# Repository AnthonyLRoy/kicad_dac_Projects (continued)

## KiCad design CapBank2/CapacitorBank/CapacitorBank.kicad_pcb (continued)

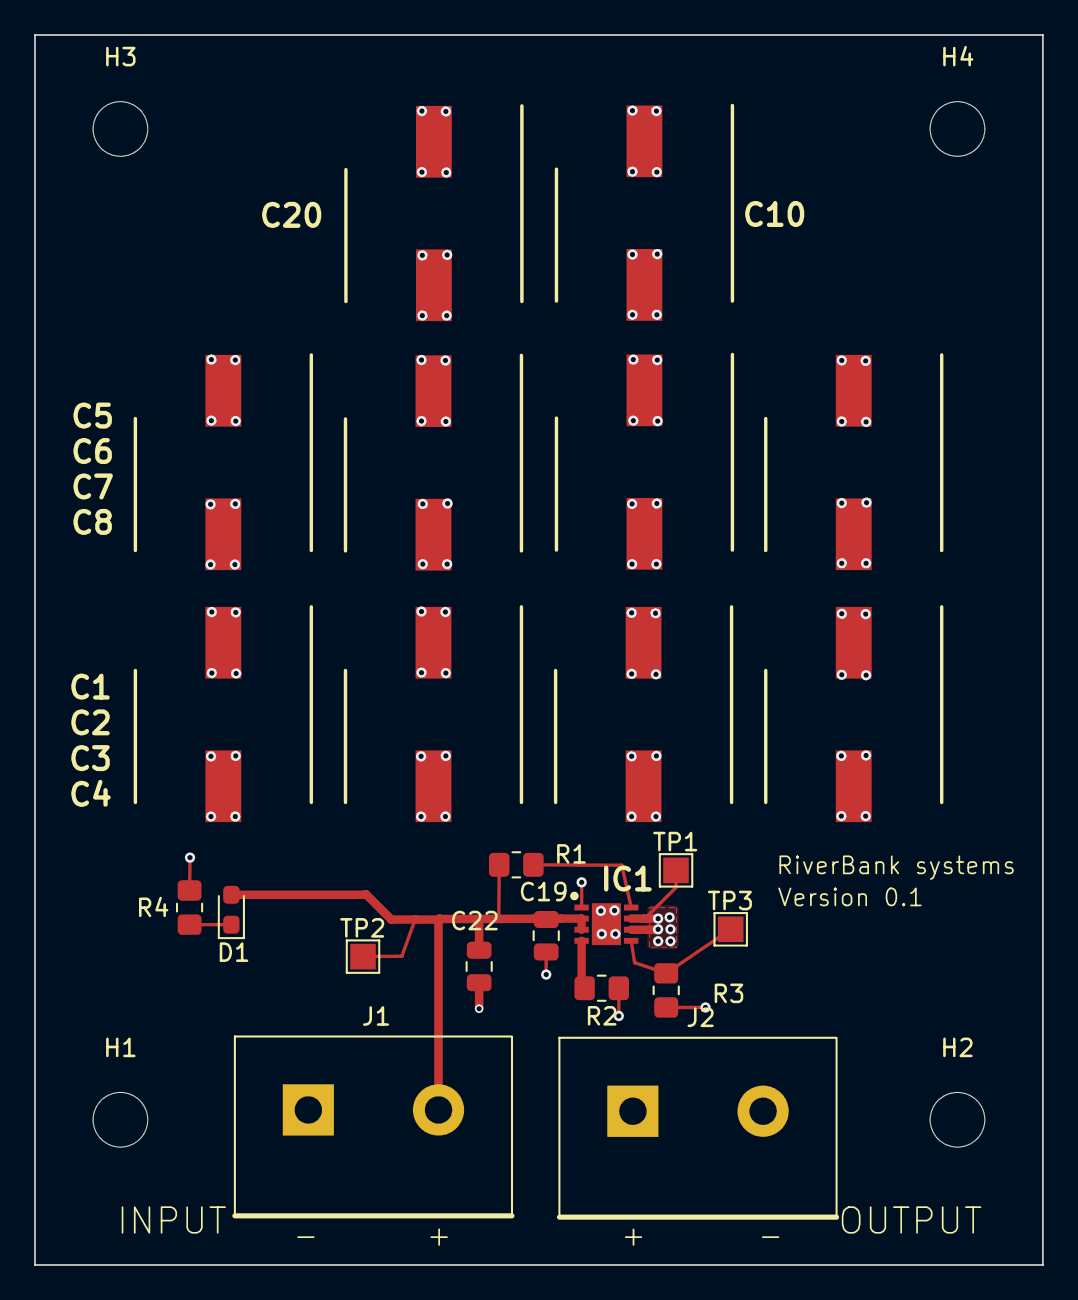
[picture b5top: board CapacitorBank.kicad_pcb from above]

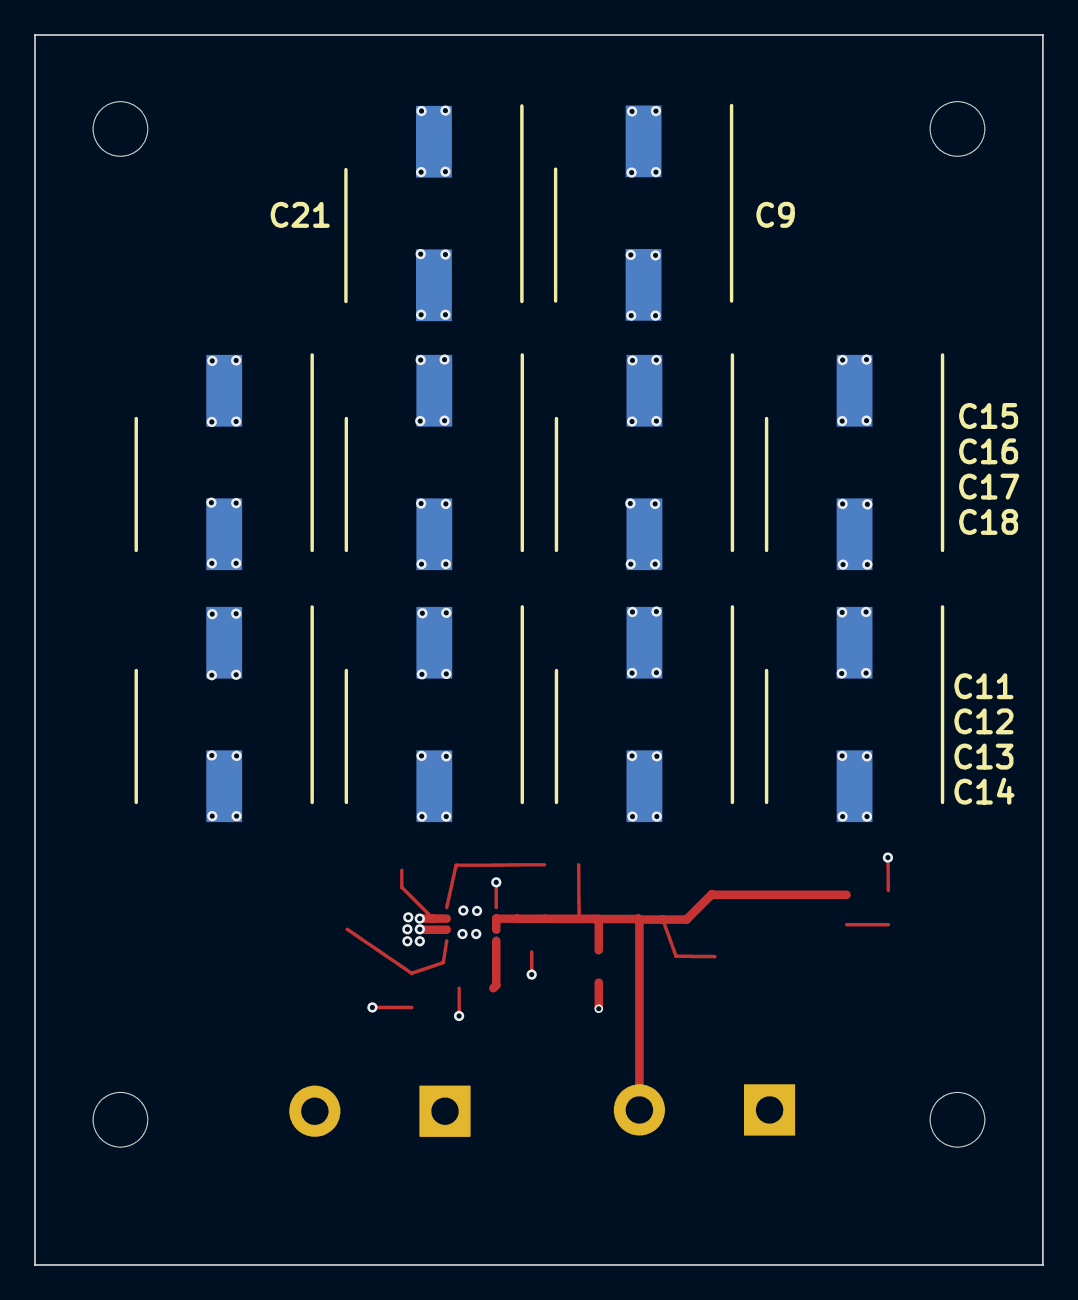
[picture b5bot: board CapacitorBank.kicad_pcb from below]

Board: 4 copper layers, 59.0 x 72.0 mm, 37 parts (10 on the bottom side), 7 nets.

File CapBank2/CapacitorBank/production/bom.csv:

Designator,Footprint,Quantity,Value,LCSC Part #
"C1, C10, C11, C12, C13, C14, C15, C16, C17, C18, C2, C20, C21, C3, C4, C5, C6, C7, C8, C9",CAPAE1030X1270N,20,875075361005,
C19,0805,1,0.1uf,
C22,0805,1,47u,
D1,0603,1,LED,
"H1, H2, H3, H4",MountingHole_3.2mm_M3,4,MountingHole,
IC1,SON65P300X300X100-9N-D,1,TPS2556QDRBTQ1,
"J1, J2",TerminalBlock_483132_2P_P7.62mm,2,Screw_Terminal_01x02,
R1,0805,1,100k,
R2,0805,1,10k,
R3,0805,1,160k,
R4,0805,1,1k,
"TP1, TP2, TP3",TestPoint_Pad_1.5x1.5mm,3,TestPoint,

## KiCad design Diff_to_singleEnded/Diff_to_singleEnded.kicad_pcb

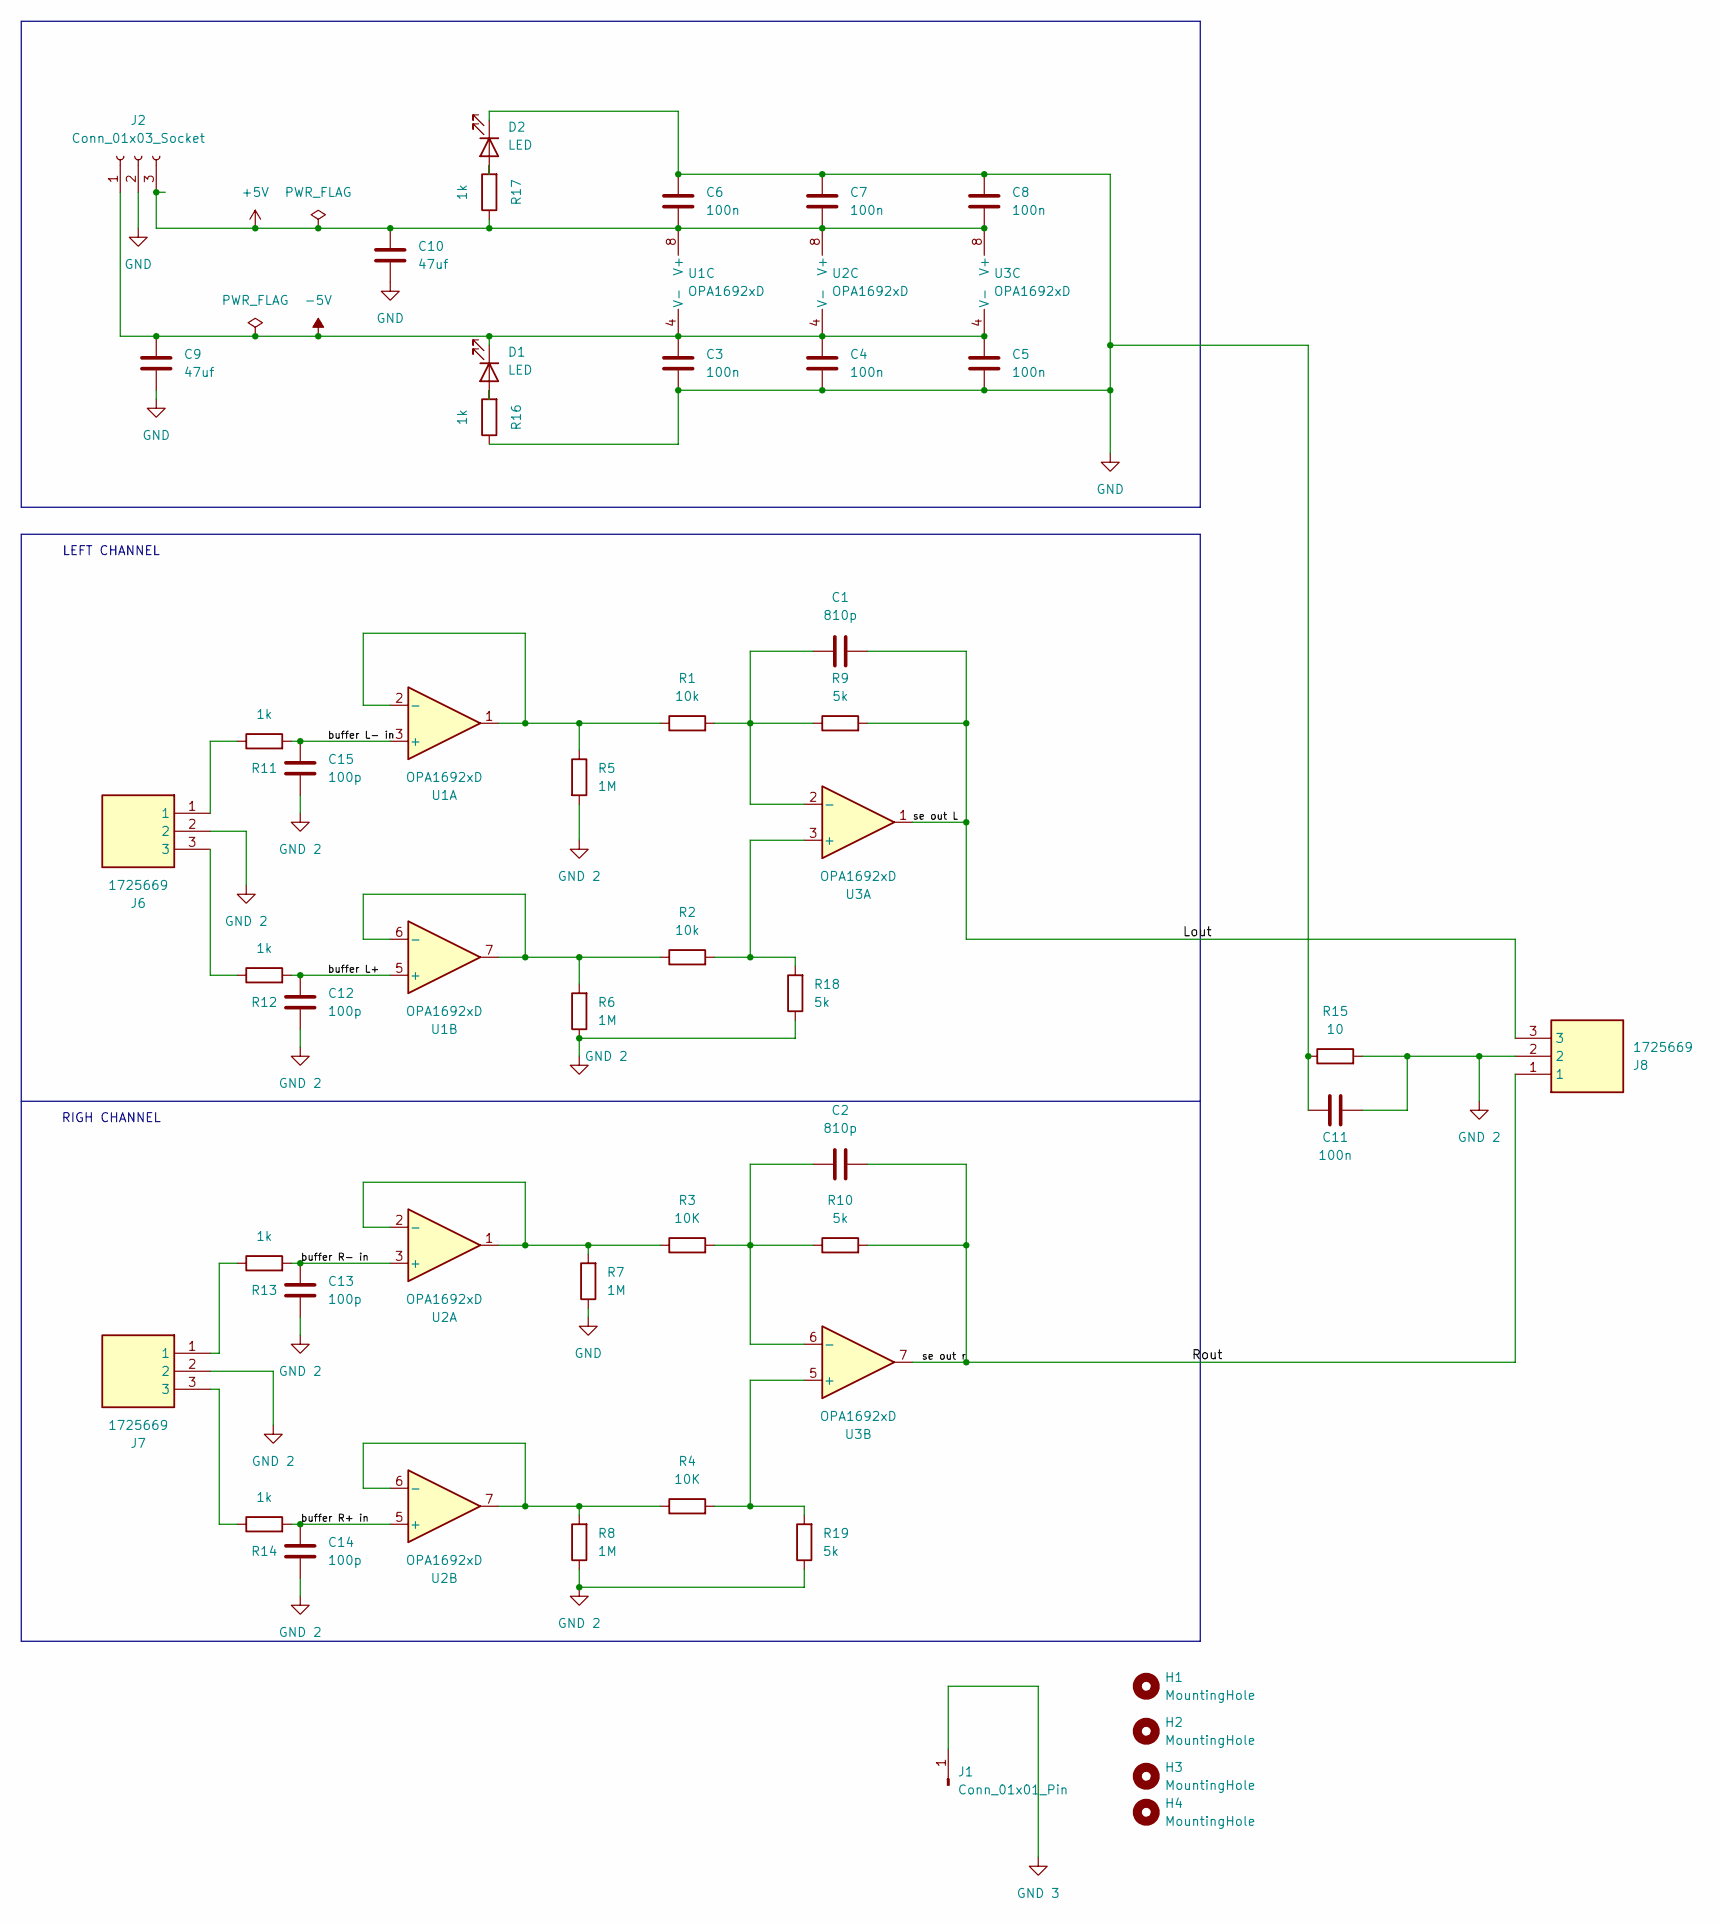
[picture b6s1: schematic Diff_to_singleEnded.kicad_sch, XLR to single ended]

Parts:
C1, C2: 810p; C_1206_3216Metric
C3, C4, C5, C6, C7, C8, C11: 100n; C_0805_2012Metric_Pad1.18x1.45mm_HandSolder
C9, C10: 47uf; CAPC3225X280N
C12, C13, C14, C15: 100p; C_0805_2012Metric
D1, D2: LED; LEDC2012X40N
H1, H2, H3, H4: MountingHole; MountingHole_2.7mm_M2.5
J1: Conn_01x01_Pin; PinHeader_1x01_P1.00mm_Vertical
J2: Conn_01x03_Socket; PhoenixContact_MCV_1,5_3-G-3.81_1x03_P3.81mm_Vertical
J6, J7, J8: 1725669; Mouser Part Number 651-1725669
R1, R2: 10k; R_Axial_DIN0309_L9.0mm_D3.2mm_P12.70mm_Horizontal
R3, R4: 10K; R_Axial_DIN0309_L9.0mm_D3.2mm_P12.70mm_Horizontal
R5, R6, R7, R8: 1M; R_Axial_DIN0309_L9.0mm_D3.2mm_P12.70mm_Horizontal
R9, R10, R18, R19: 5k; R_Axial_DIN0309_L9.0mm_D3.2mm_P12.70mm_Horizontal
R11, R12, R13, R14, R16, R17: 1k; R_0805_2012Metric
R15: 10; R_0603_1608Metric
U1, U2, U3: OPA1692xD; SOIC-8_3.9x4.9mm_P1.27mm

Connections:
+5V: C6.2, C7.2, C8.2, C10.1, J2.3, R17.1, U1.8 (V+), U2.8 (V+), U3.8 (V+)
-5V: C3.1, C4.1, C5.1, C9.1, D1.1 (K), J2.1, U1.4 (V-), U2.4 (V-), U3.4 (V-)
/Lout: C1.2, J8.3, R9.2, U3.1
/Rout: C2.2, J8.1, R10.2, U3.7
/buffer L+: C12.2, R12.2, U1.5 (+)
/buffer L- in: C15.2, R11.2, U1.3 (+)
/buffer R+ in: C14.2, R14.2, U2.5 (+)
/buffer R- in: C13.2, R13.2, U2.3 (+)
GND: C3.2, C4.2, C5.2, C6.1, C7.1, C8.1, C9.2, C10.2, C11.1, D2.1 (K), J2.2, R7.1, R15.1, R16.1
GND 2: C11.2, C12.1, C13.1, C14.1, C15.1, J6.2, J7.2, J8.2, R5.2, R6.1, R8.1, R15.2, R18.1, R19.1
GND 3: J1.1 (Pin_1_1)
unnamed: D1.2 (A), R16.2
unnamed: D2.2 (A), R17.2
unnamed: J6.1, R11.1
unnamed: J6.3, R12.1
unnamed: J7.1, R13.1
unnamed: J7.3, R14.1
unnamed: R1.1, R5.1, U1.1, U1.2 (-)
unnamed: R2.1, R6.2, U1.6 (-), U1.7
unnamed: R3.1, R7.2, U2.1, U2.2 (-)
unnamed: R4.1, R8.2, U2.6 (-), U2.7
unnamed: R2.2, R18.2, U3.3 (+)
unnamed: C1.1, R1.2, R9.1, U3.2 (-)
unnamed: R4.2, R19.2, U3.5 (+)
unnamed: C2.1, R3.2, R10.1, U3.6 (-)

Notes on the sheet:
LEFT CHANNEL
RIGH CHANNEL

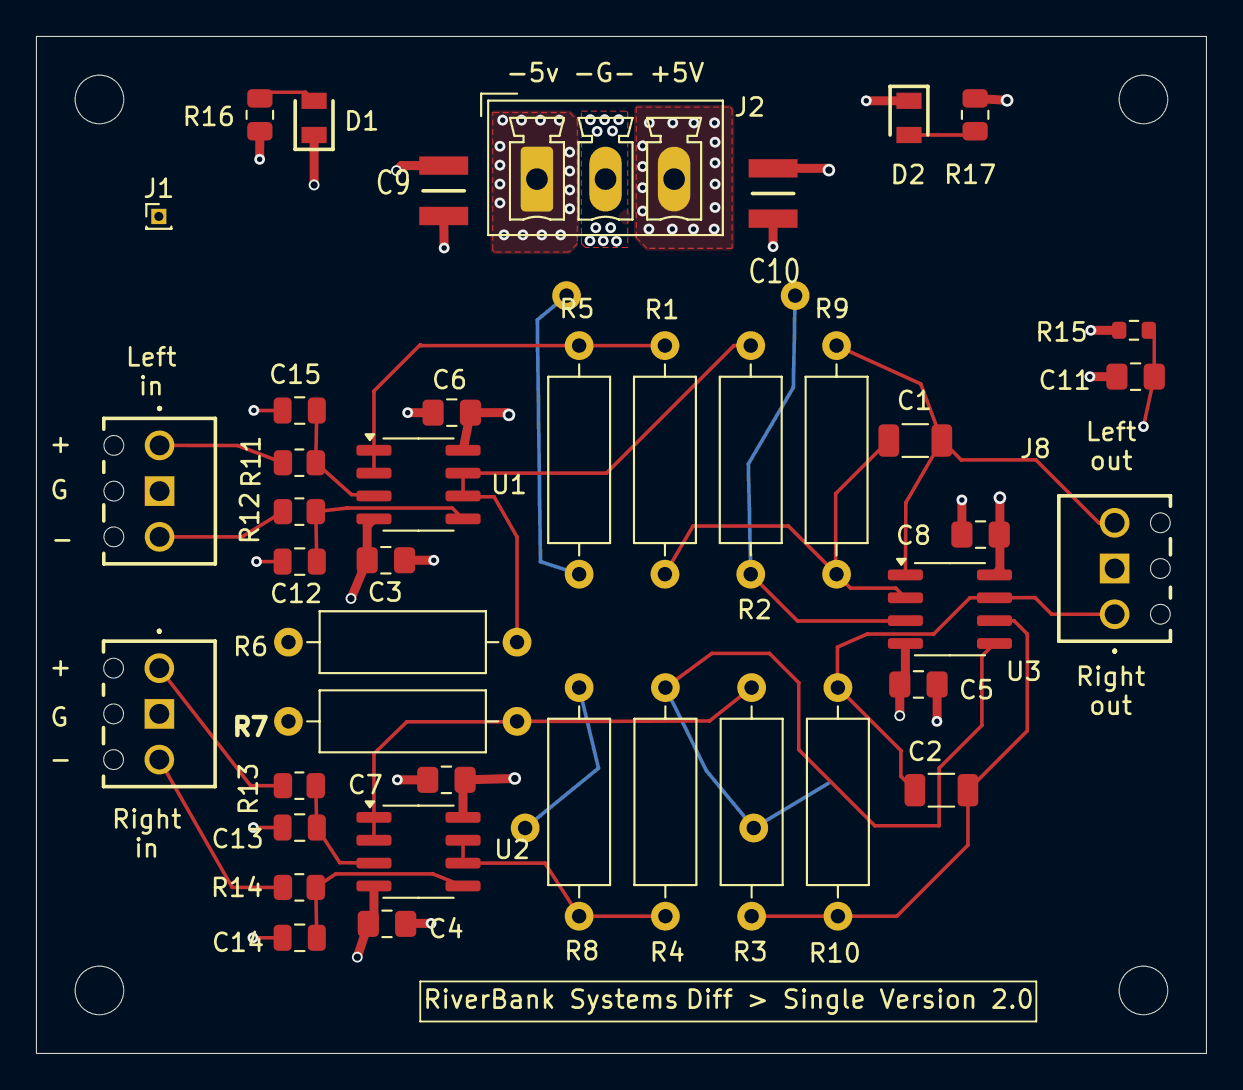
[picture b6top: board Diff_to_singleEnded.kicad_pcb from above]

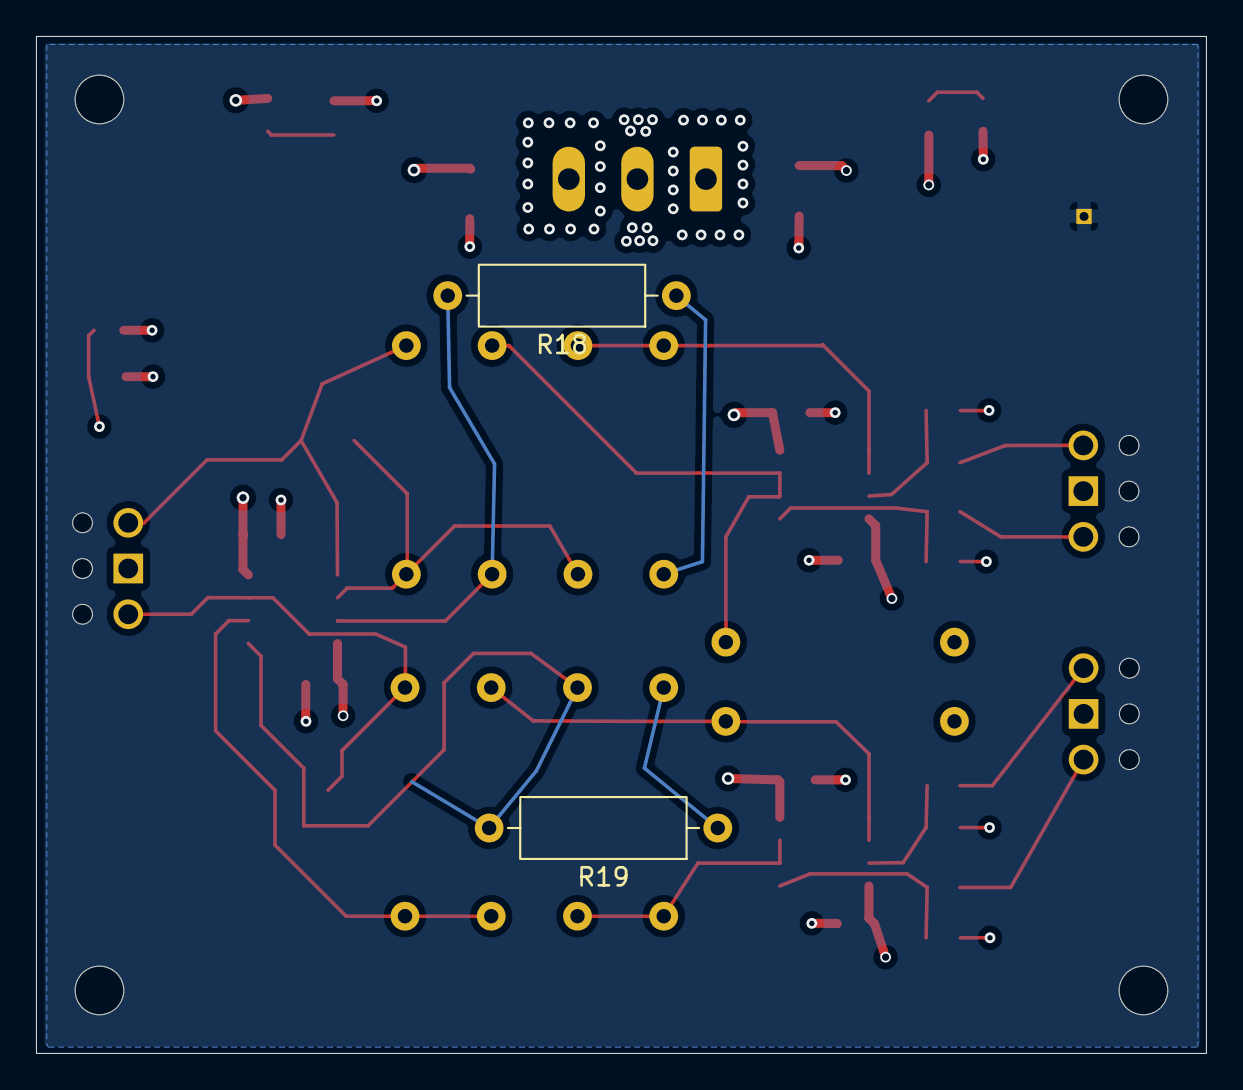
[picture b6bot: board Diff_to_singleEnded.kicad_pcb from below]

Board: 6 copper layers, 65.0 x 56.5 mm, 48 parts (2 on the bottom side), 24 nets.

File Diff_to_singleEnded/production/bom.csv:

Designator,Footprint,Quantity,Value,LCSC Part #
"C1, C2",1206,2,810p,
"C10, C9",CAPC3225X280N,2,47uf,
"C11, C3, C4, C5, C6, C7, C8",0805,7,100n,
"C12, C13, C14, C15",0805,4,100p,
"D1, D2",LEDC2012X40N,2,LED,
"H1, H2, H3, H4",MountingHole_2.7mm_M2.5,4,MountingHole,
J1,PinHeader_1x01_P1.00mm_Vertical,1,Conn_01x01_Pin,
J2,"PhoenixContact_MCV_1,5_3-G-3.81_1x03_P3.81mm_Vertical",1,Conn_01x03_Socket,
"J6, J7, J8",1725669,3,1725669,
"R1, R2, R3, R4",R_Axial_DIN0309_L9.0mm_D3.2mm_P12.70mm_Horizontal,4,10k,
"R10, R9",R_Axial_DIN0309_L9.0mm_D3.2mm_P12.70mm_Horizontal,2,5k,
"R11, R12, R13, R14, R16, R17",0805,6,1k,
R15,0603,1,10,
"R5, R6, R7, R8",R_Axial_DIN0309_L9.0mm_D3.2mm_P12.70mm_Horizontal,4,1M,
"U1, U2, U3",SOIC-8_3.9x4.9mm_P1.27mm,3,OPA1692xD,

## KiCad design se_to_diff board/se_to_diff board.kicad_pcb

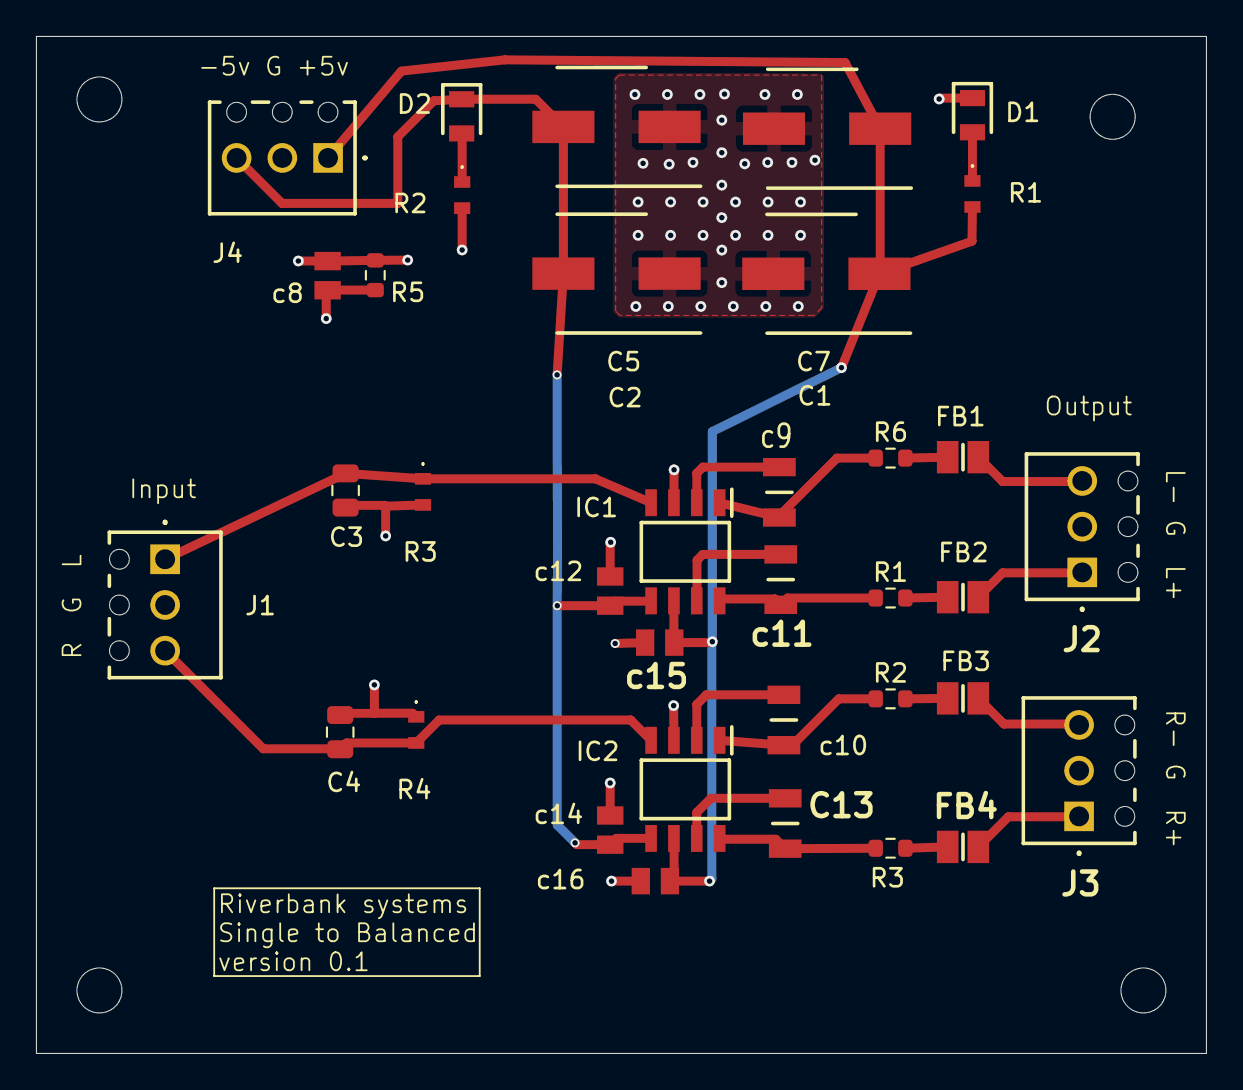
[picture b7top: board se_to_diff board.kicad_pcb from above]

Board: 4 copper layers, 65.0 x 56.5 mm, 40 parts (0 on the bottom side), 24 nets.

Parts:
C1, C2, C5, C7: 47u; CAPAE660X800N
C3, C4: 220p; C_0805_2012Metric
C13: 10u; CAPC3216X229N
D1, D2: LS_R976; LEDC2012X40N
FB1, FB2, FB3, FB4: NFZ2MSD101SZ10L; BEADC2016X120N
H1, H2, H3, H4: MountingHole; MountingHole_2.5mm
IC1, IC2: 1646S08-U; SOIC127P602X173-8N
J1, J2, J3, J4: 1725669
R1, R2#2, R3: 22; R_0603_1608Metric
R1#2, R2: 3k; ERJH3
R3#2, R4: 47k; ERJH3
R5: 10R; R_0603_1608Metric
R6: 22R; R_0603_1608Metric
c8, c12, c14, c15, c16: 100n; CAPC2012X94N
c9, c10, c11: 10u; CAPC3216X229N

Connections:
/Sout L +: FB2.1, R1.2
/Sout L -: FB1.1, R6.2
/Sout R +: FB4.1, R3.2
/Sout R -: FB3.1, R2#2.2
/in L: C3.2, IC1.4 (IN), J1.1, R3#2.1
/in R: C4.1, IC2.4 (IN), J1.3, R4.2
/out L +: IC1.8 (OUT+), R1.1, c11.2
/out L -: IC1.1 (OUT-), R6.1, c9.2
/out R +: C13.2, IC2.8 (OUT+), R3.1
/out R -: IC2.1 (OUT-), R2#2.1, c10.2
GND: C3.1, C4.2, IC1.3 (GND), IC2.3 (GND), J1.2, J2.2, J3.2, R3#2.2, R4.1, R5.2, c8.1
GND2: C1.2, C2.1, C5.1, C7.2, D1.1 (K), J4.2, R2.2, R5.1, c8.2, c12.1, c14.1, c15.1, c16.1
unnamed: D1.2 (A), R1#2.1
unnamed: D2.2 (A), R2.1
unnamed: FB1.2, J2.3
unnamed: FB2.2, J2.1
unnamed: FB3.2, J3.3
unnamed: FB4.2, J3.1
unnamed: IC1.7 (SNS+), c11.1
unnamed: IC1.2 (SNS-), c9.1
unnamed: C13.1, IC2.7 (SNS+)
unnamed: IC2.2 (SNS-), c10.1
VCC: C1.1, C7.1, IC1.6 (VCC), IC2.6 (VCC), J4.1, R1#2.2, c15.2, c16.2
VEE: C2.2, C5.2, D2.1 (K), IC1.5 (VEE), IC2.5 (VEE), J4.3, c12.2, c14.2

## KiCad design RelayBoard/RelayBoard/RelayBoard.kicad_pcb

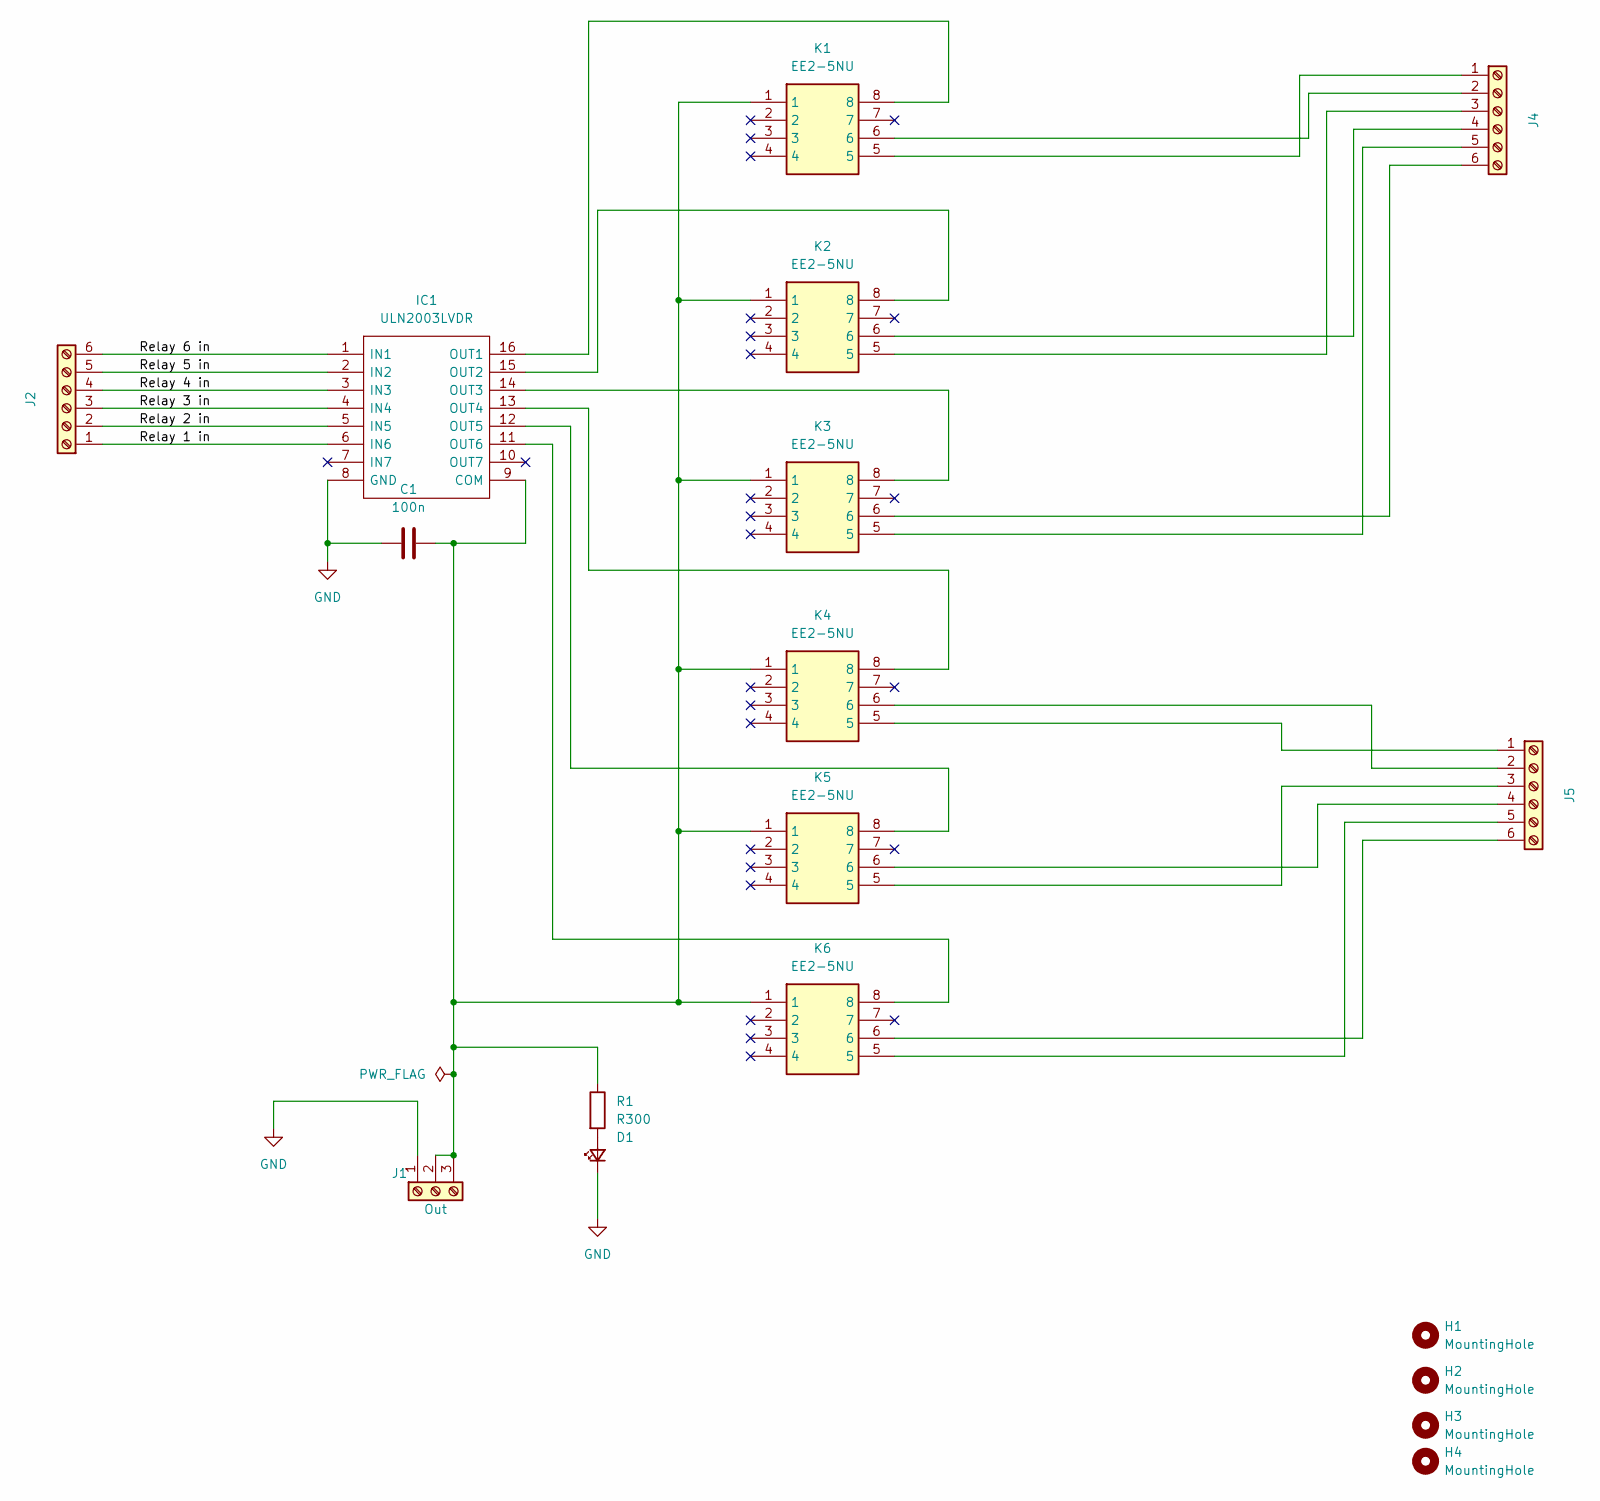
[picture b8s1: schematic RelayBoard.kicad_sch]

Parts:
C1: 100n; C_0805_2012Metric_Pad1.18x1.45mm_HandSolder
D1: LS_R976; LEDC2012X40N; Mouser Part Number 720-LSR976D5178
H1, H2, H3, H4: MountingHole; MountingHole_2.7mm_M2.5
IC1: ULN2003LVDR; SOIC127P780X200-16N; Manufacturer_Part_Number ULN2003LVDR; Mouser Part Number 595-ULN2003LVDR
J1: Out; PinHeader_1x03_P2.54mm_Vertical
J2, J4, J5: Buffer; PinHeader_1x06_P2.54mm_Vertical
K1, K2, K3, K4, K5, K6: EE2-5NU; Mouser Part Number 80-EE2-5NU
R1: R300; R_0603_1608Metric_Pad0.98x0.95mm_HandSolder

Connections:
/Relay 1 in: IC1.6 (IN6), J2.1
/Relay 2 in: IC1.5 (IN5), J2.2
/Relay 3 in: IC1.4 (IN4), J2.3
/Relay 4 in: IC1.3 (IN3), J2.4
/Relay 5 in: IC1.2 (IN2), J2.5
/Relay 6 in: IC1.1 (IN1), J2.6
GND: C1.1, D1.1 (K), IC1.8 (GND), J1.1
unnamed: D1.2 (A), R1.2
unnamed: C1.2, IC1.9 (COM), J1.2, J1.3, K1.1, K2.1, K3.1, K4.1, K5.1, K6.1, R1.1
unnamed: IC1.16 (OUT1), K1.8
unnamed: IC1.15 (OUT2), K2.8
unnamed: IC1.14 (OUT3), K3.8
unnamed: IC1.13 (OUT4), K4.8
unnamed: IC1.12 (OUT5), K5.8
unnamed: IC1.11 (OUT6), K6.8
unnamed: J4.1, K1.5
unnamed: J4.2, K1.6
unnamed: J4.3, K2.5
unnamed: J4.4, K2.6
unnamed: J4.5, K3.5
unnamed: J4.6, K3.6
unnamed: J5.1, K4.5
unnamed: J5.2, K4.6
unnamed: J5.3, K5.5
unnamed: J5.4, K5.6
unnamed: J5.5, K6.5
unnamed: J5.6, K6.6

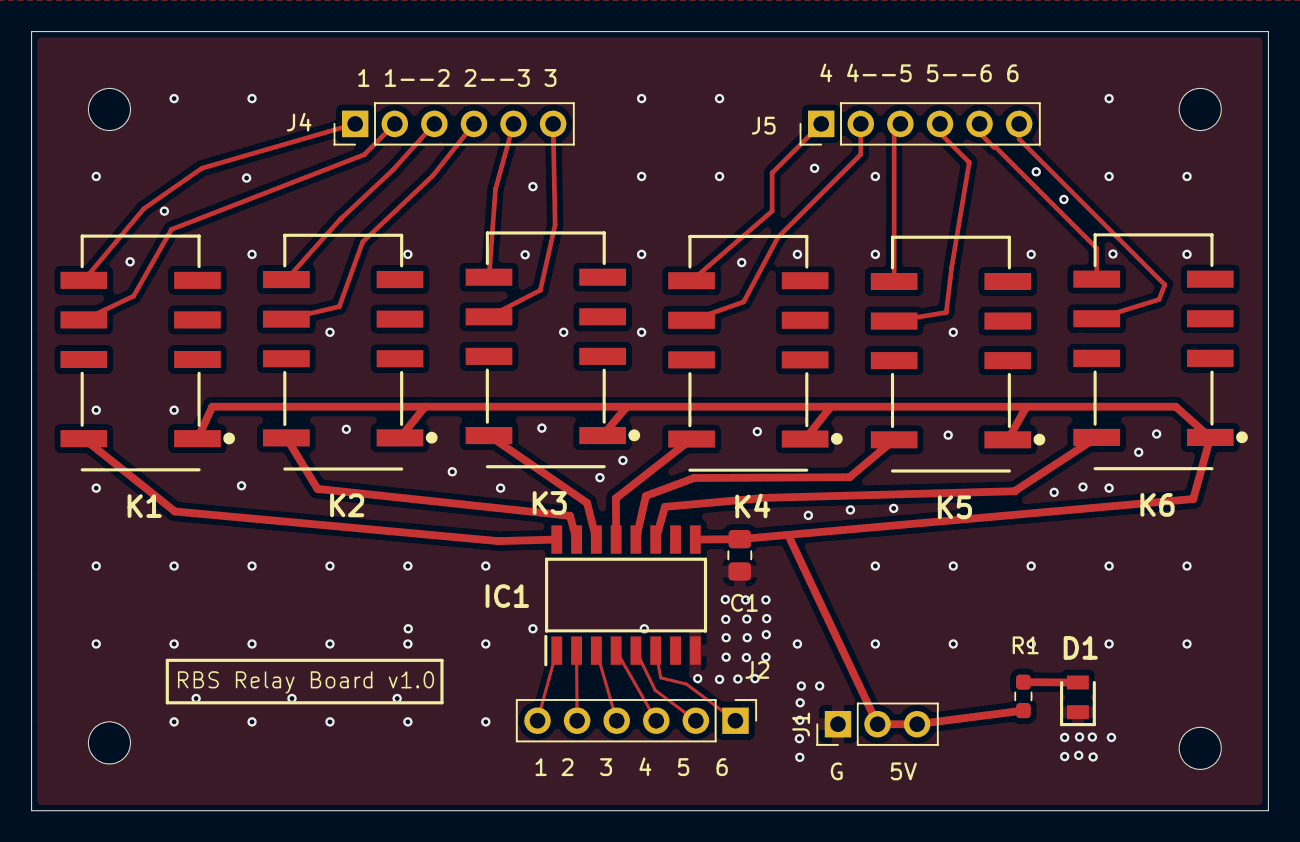
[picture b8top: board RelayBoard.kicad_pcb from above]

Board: 2 copper layers, 79.4 x 50.0 mm, 18 parts (0 on the bottom side), 27 nets.
